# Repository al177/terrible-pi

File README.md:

# terrible-pi

*A supercomputer, but fun sized. And not super.*

In this repo you'll find hardware designs for the Terrible-Pi, a cluster
computer made from four Raspberry Pi Zero boards used as compute elements
and one Raspberry Pi Zero W as a head node and network router.

terrible-pi is based around a USB backplane that powers and interconnects
all five Pi Zeros and allows the head node to control power to each of the
compute nodes.  The USB boot feature of the Pi Zero is used to automate
deployment of new OS images to each compute node.

Up to date news on this project can be found at [this Hackaday project.](https://hackaday.io/project/27142-terrible-cluster)

Repo Contents
-------------
The terrible_pcb directory has a board design for the backplane and a 3D printable case.  See terrible_pcb/README for instructions for printing the case and the backplane board.

`etc` contains config files to be copied on top of the Raspbian install for
the head node.

wpa_supplicant.conf is a template WiFi config for the head node.  This is used
for headless setup of the head node Raspbian SD card for remote SSH access.

`nodeimg_build.sh` is a script for extracting a Raspbian distribution image into
a set of files used to deploy new compute nodes.

`node_init.sh` is a script used to upload the compute node Raspbian generated
by `nodeimg_build.sh` to the SD card of a compute node.

terrible-pi Install and Usage Guide
===================================

Setting up a terrible-pi cluster head node
------------------------------------------

1. Get the latest Raspbian (https://downloads.raspberrypi.org/raspbian_lite_latest)
   and install to a microSD
   
2. Mount the first (FAT) partition of the card on a PC.
		
3. Copy "wpa_supplicant.conf" from this repo to the card.  Edit it so that
   "YOUR_SSID" is replaced by the WiFi network name that you want the head node
   to connect to, and "YOUR_PASSPHRASE" is replaced by the network's key.  Use
   your Google-fu if you can't get it to work.
		
4. Create an empty file on the card named "ssh".  Use the UNIX command "touch
   ssh" or just open and save a new file "ssh" with your text editor.
		
5. Boot the microSD on the Pi Zero W
		
6. After 4-5 minutes, try SSHing as "pi" to the Zero W with the hostname
   "raspberrypi", "raspberrypi.lan", or "raspberrypi.local".  Use the password
   "raspberry".  If your router isn't serving DNS for local domains, you may
   have to check the router's DHCP lease logs to see what IP the head node has.
		
7. Now that you're logged into the Pi Zero W, update to the latest Raspbian
   packages:

```
sudo apt-get -y update && sudo apt-get -y upgrade
```
			
8. Install the necessary packages:
			
```
sudo apt-get -y install libusb-1.0-0-dev nfs-kernel-server git \
pdsh udhcpd iptables bridge-utils
```
9. Build and install the USB hub tool:

```
cd
git clone https://github.com/mvp/uhubctl.git
pushd uhubctl
make
sudo cp uhubctl /usr/local/bin/.
sudo chown root:root /usr/local/bin/uhubctl
popd
```
10. Build and install the USB boot tool:
	
```
git clone https://github.com/raspberrypi/usbboot.git
pushd usbboot
make
sudo cp rpiboot /usr/local/bin/.
sudo mkdir /usr/share/rpiboot
sudo cp -a msd /usr/share/rpiboot
sudo chown -R root:root /usr/share/rpiboot
sudo chown -R root:root /usr/local/bin/rpiboot
popd
```
11. Get this repo on the Pi:

```
git clone https://github.com/al177/terrible-pi.git
```

12. Copy the config files for the DHCP server, networks, NFS, SSH, and
hosts, hostname, and startup scripts:

```
sudo chown -R root:root /home/pi/terrible-pi/etc			
sudo cp -a /home/pi/terrible-pi/etc/* /etc/.
```		
13. Enable necessary services:

```
sudo systemctl enable udhcpd
sudo systemctl enable rpcbind
sudo systemctl enable nfs-kernel-server
```
14. Create an NFS directory for the clients:

```
sudo mkdir /srv/pihome
sudo chown pi:pi /srv/pihome
chmod 755 /srv/pihome
mkdir /srv/pihome/.ssh
chmod 700 /srv/pihome/.ssh
```

15. Reboot the head node.

16. SSH to the head node again. The config files copied over have changed the
    hostname to "head".  So if you connected as "raspberrypi.lan",
    "raspberrypi", or "raspberrypi.local" above, use "head.lan", "head", or
    "head.local" when reconnecting.

17. Make an empty passphrase SSH key so the head can automatically connect to
    the nodes:

```
ssh-keygen -t rsa -f /srv/pihome/.ssh/terrible.rsa -N ""
cp /srv/pihome/.ssh/terrible.rsa.pub /srv/pihome/.ssh/authorized_keys
chmod 600 /srv/pihome/.ssh/authorized_keys
mkdir -p ~/.ssh
chmod 700 ~/.ssh
cp /srv/pihome/.ssh/terrible.rsa ~/.ssh/.
```

Setting up terrible cluster compute nodes
-----------------------------------------

### Creating the compute node filesystem

1. Get the Raspbian Lite zip file on the head node in /home/pi.  This can be
   the zip used to create the head node microSD card, or can be downloaded by:

```
wget --trust-server-names https://downloads.raspberrypi.org/raspbian_lite_latest
```
	 
Note the filename that it downloads as.

2. Prep the boot image:

```
sudo terrible-pi/nodeimg_build.sh 2017-09-07-raspbian-stretch-lite.zip
```
	
This will take 10-15 minutes.  The result will be a directory "tcboot"
that contains the boot files and filesystems for the nodes.  This process
needs to be repeated only when changing or upgrading the Raspbian install on
the compute nodes.

### Deploying Raspbian to the compute nodes

1. Insure that the microSD cards in nodes do not contain the Raspberry Pi
   bootloader, or the USB boot method used to manage this cluster will not work.
   Insure that "bootcode.bin" does not exist in the root of any of the
   partitions on any of the cards.  If in doubt, do a full erase on the SD card
   to wipe out the bootloader in any of the partitions.
	 
2. Turn off all the nodes.  If the nodes all power up in bootstrap mode
   simultaneously, the image transfer script won't work.

```
sudo uhubctl -r 4 -a off
```

3. Transfer the SD filesystem to each node, looping over all nodes in series:

```
for N in 1 2 3 4; do sudo terrible-pi/node_init.sh tcboot $N; done
```

This takes 5-10 minutes per node depending on the speed of the SD cards
on the compute node Pi Zeros.

Terrible cluster management
---------------------------

### Booting the cluster

To boot the compute nodes, first start the rpiboot server in another
terminal session:

```
sudo rpiboot -o -l -d /home/pi/tcboot
```

Then cycle power on all of the nodes:

```
sudo uhubctl -r 4 -a cycle
```

The boot will take 2-3 minutes.  The nodes should be pingable once they are
done.  

### Connecting to the nodes

Before SSHing to a node in any given session, start the key agent and add
the SSH key:

```
eval `ssh-agent`
ssh-add ~/.ssh/terrible.rsa
```

You can SSH to a node by name:

```
ssh node1
```

Or you can run a command on all nodes with pdsh:

```
pdsh -R ssh -w node1,node2,node3,node4 hostname
```

Raspberry Pi Zero 1.3 models
[pi0computer.stl and pi0sdcard.stl](https://www.thingiverse.com/thing:2101674)
are created by jdhorvat and licensed CC-BY-NC.  [OpenSCAD parametric fan model](https://www.thingiverse.com/thing:625905) is created by GelatinousSlime and licensed CC-BY-SA. All other files in this tree are by Andrew Litt and licensed as 
[CC-BY-SA.](https://creativecommons.org/licenses/by-sa/4.0/)

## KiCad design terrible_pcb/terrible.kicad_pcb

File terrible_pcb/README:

Hardware design for the Terrible Cluster.

1) Backplane board

terrible.pro is the KiCad project for the Terrible Cluster backplane board.  All components needed to create fabbable output are in this project, however due to license restrictions the 3D models needed to render the assembly are not included.

Pre-built gerbers for the v0.1 release of the board are in the directory gerber_v0.1.  These are fab-ready and can be zipped and sent off as-is.

terrible_v1a_bom.csv is a CSV format BOM for the backplane.  It can be imported to a Digi-Key cart for convenience.

BOM history
-----------
v1  - Initial BOM for PCB v0.1
v1a - Corrected microUSB B to match the current footprint, add insulator
      spacer for crystal Y1

After assembling the backplane, flush cut all of the through hole pins to under 1mm, or it may not fit in the case.

2) Case

terrible_case.scad is an OpenSCAD model for a 3D printed enclosure for the Terrible Cluster.  It is a single piece into which the backplane and Zero nodes can slide.  A 40mm x 40mm x 10mm 5V fan is friction-fit into the open end, and provides cooling for the cluster.  The cluster board assembly is held in place by a piece of 1.75mm filament fed through holes at the open side of the backplane PCB channel.

terrible_case.stl is a printable file for the case rendered from terrible_case.scad.  This case is sensitive to printer tolerances, so if parts of the case print too tight or loose, it may be necessary to customize the SCAD file and regenerate the .stl.

The fan is wired to the two pin power pads on the backplane.  A 2x1 0.1" right angle header can be soldered to the pads, and a matching plug attached to the fan leads if desired, or the fan can be soldered directly to the pads.  Care should be taken to reduce slack in the fan cable to prevent any loose wire from interfering with the fan.

When sliding the cluster into the case, it may be necessary to move the Zeros side to side to get them to all fit in the slot cutouts.  It should not take much force to get the backplane to slide in all the way.

After the cluster is in the case, feed a piece of 1.75mm filament through both holes towards the back of the case.  Use flush cutters to clip the filament even with the side of the case on both sides.  This will prevent the cluster from sliding backwards into the fan, especially when inserting a microUSB power cable.  To take apart the cluster, push the filament through with a paperclip and pull it out from the other side.

The fan uses a friction fit to hold it in the back of the case.  Exact outer dimensions of these fans can vary slightly, so the fan cutout is intentionally slightly oversized.  Use a piece of folded paper or layers of tape on one side of the fan as a shim to secure the fan.

The SCAD file can render the case alone in an orientation for printing, or render the case along with a model of the cluster and the fan to show the finished cluster.  Set "PRODUCTION=true" near the top of the SCAD to render for printing, and "PRODUCTION=false" to render the internal parts as well.

3) Cluster model

terrible.scad is an OpenSCAD model of the backplane board and the Raspberry Pi Zeros.  It is used as part of the case model for checking fitment and to render a completed Terrible Cluster.  Load it into OpenSCAD on its own to render the cluster boards.

Attributions:

-Raspberry Pi Zero model by MisterC from https://www.thingiverse.com/thing:1638529 for the 3D model.

-OpenSCAD parametric fan model by GelatinousSlime from https://www.thingiverse.com/thing:625905 for the case model.

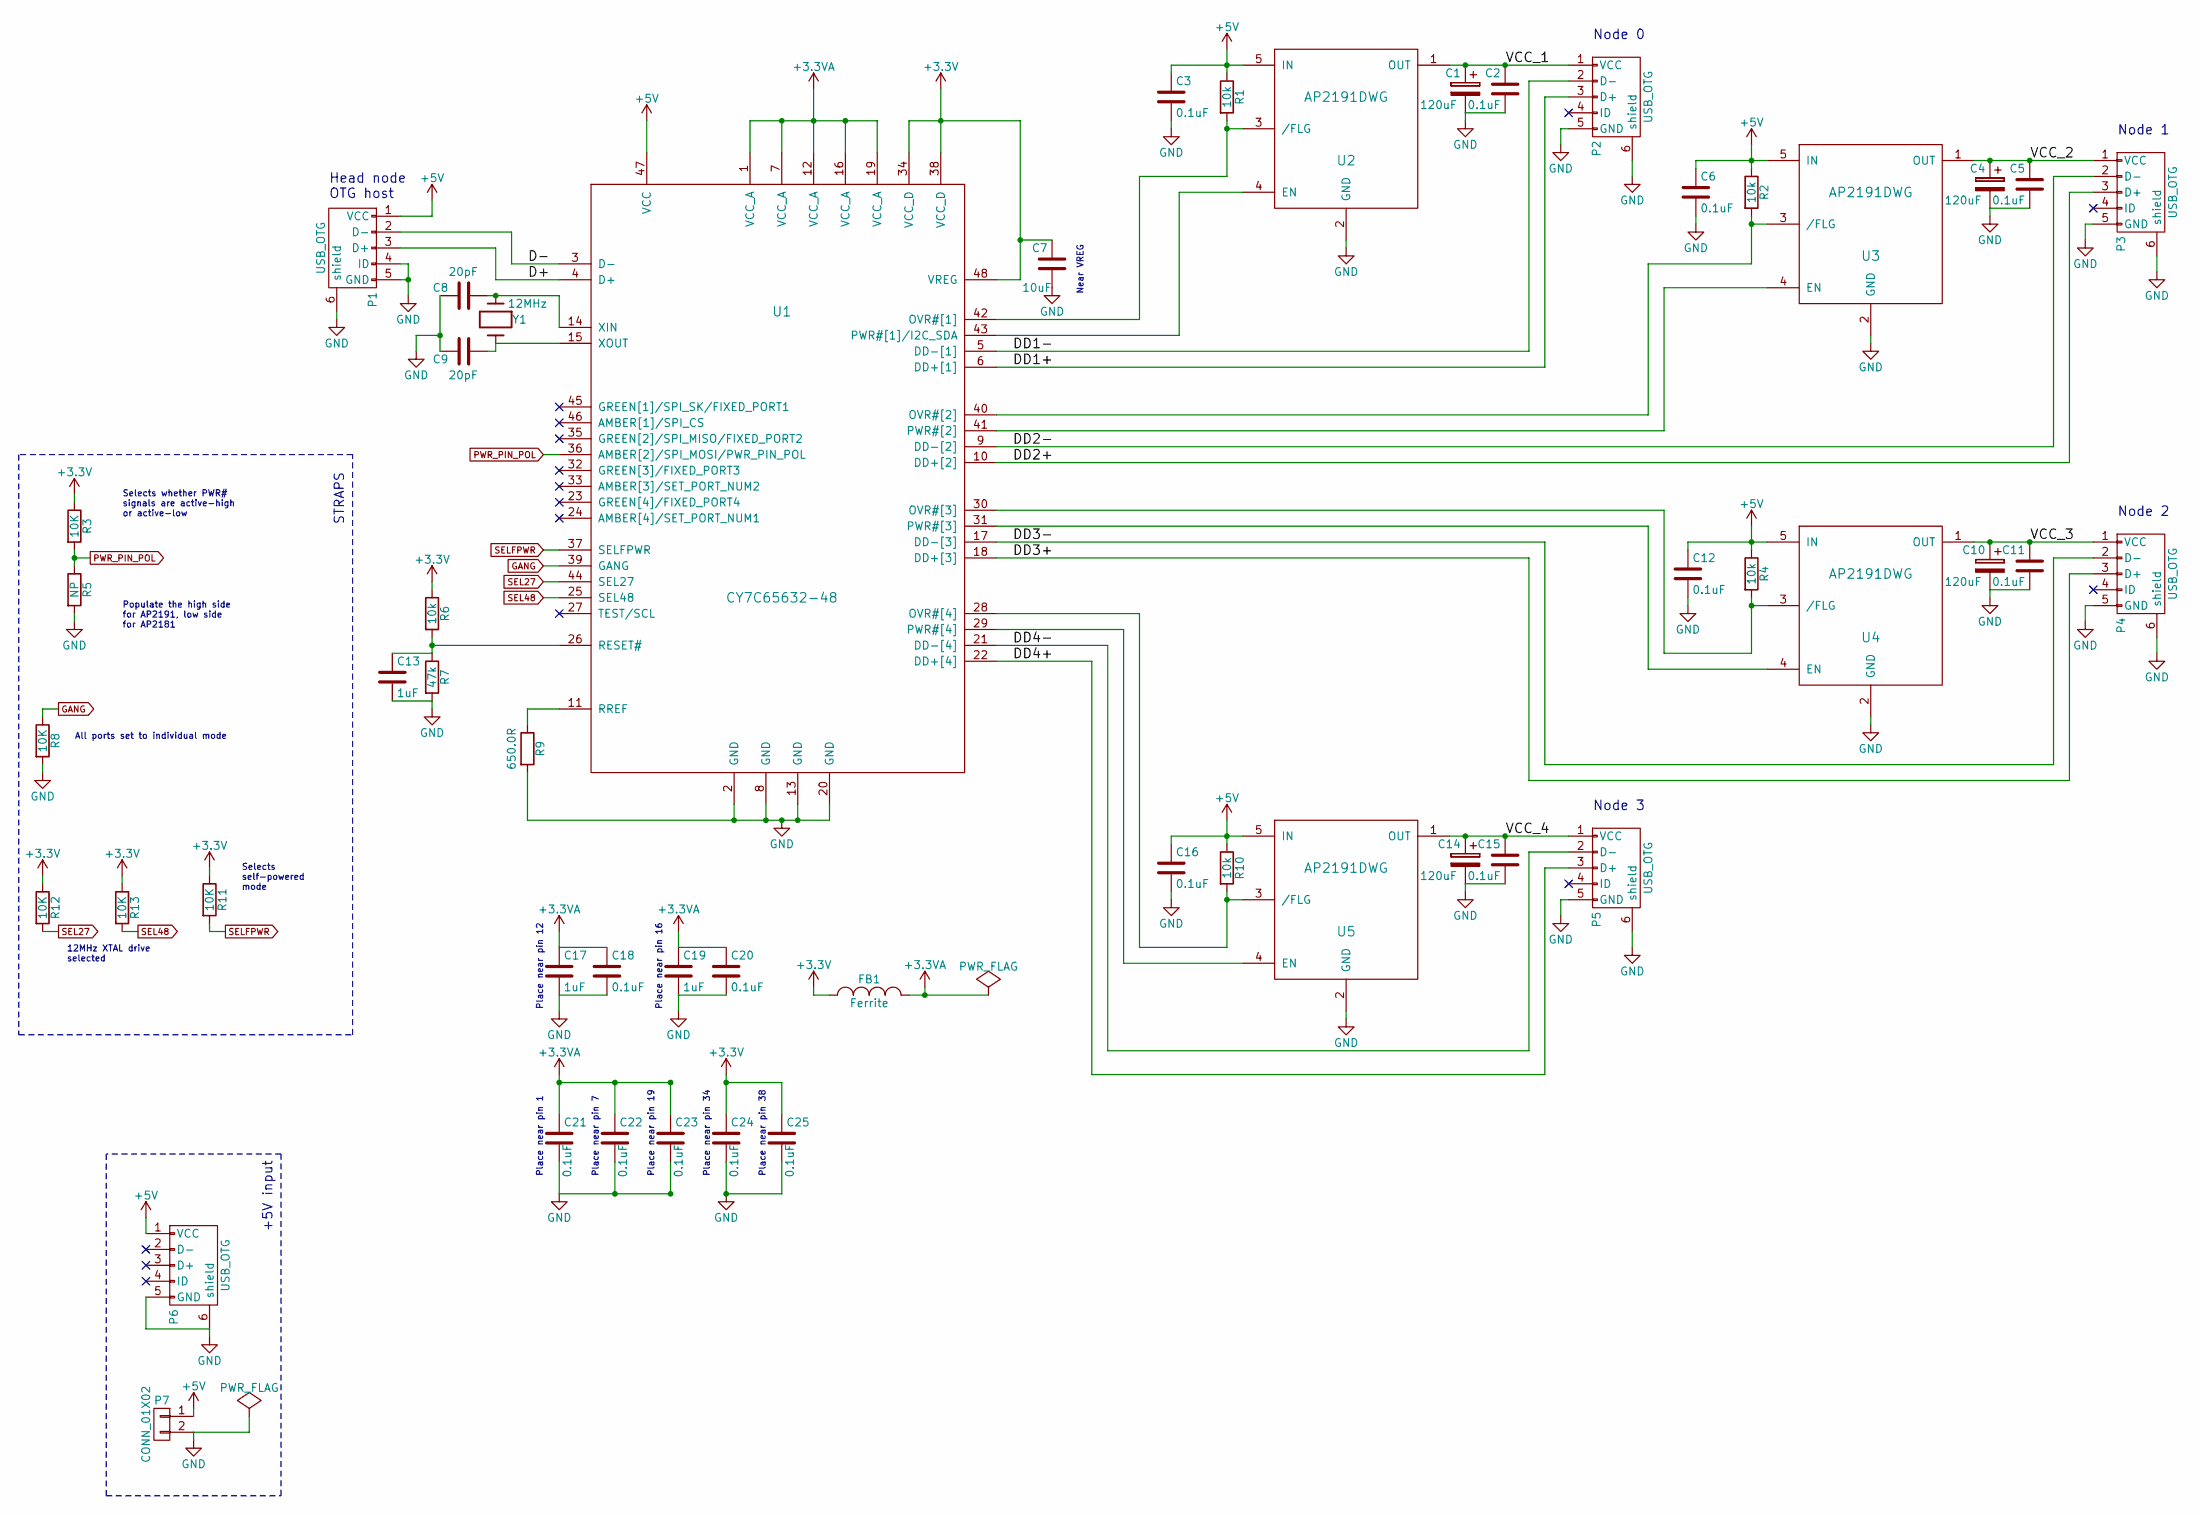
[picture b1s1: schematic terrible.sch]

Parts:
C1, C4, C10, C14: 120uF; C_Radial_D5_L11_P2.5
C2, C3, C5, C6, C11, C12, C15, C16, C18, C20, C21, C22, C23, C24, C25: 0.1uF; C_0805_HandSoldering
C7: 10uF; C_Radial_D5_L11_P2.5
C8, C9: 20pF; C_0805_HandSoldering
C13, C17, C19: 1uF; C_0805_HandSoldering
FB1: Ferrite; Choke_SMD_1206_Handsoldering
P1, P2, P3, P4, P5: USB_OTG; USB_Micro-B
P6: USB_OTG; USB_Micro-B_10103594-0001LF
P7: CONN_01X02; Pin_Header_Angled_1x02
R1, R2, R4, R6, R10: 10k; R_0603_HandSoldering
R3, R8, R11, R12, R13: 10K; R_0603_HandSoldering
R5: NP; R_0603_HandSoldering
R7: 47k; R_0603_HandSoldering
R9: 650.0R; R_0603_HandSoldering
U1: CY7C65632-48; TQFP-48_7x7mm_Pitch0.5mm
U2, U3, U4, U5: AP2191DWG; SOT-23-5
Y1: 12MHz; Crystal_HC49-SD_SMD

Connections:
+3.3VA: C17.1, C18.1, C19.1, C20.1, C21.1, C22.1, C23.1, FB1.1, U1.1 (VCC_A), U1.7 (VCC_A), U1.12 (VCC_A), U1.16 (VCC_A), U1.19 (VCC_A)
+3V3: C7.1, C24.1, C25.1, FB1.2, R3.1, R6.1, R11.1, R12.1, R13.1, U1.34 (VCC_D), U1.38 (VCC_D), U1.48 (VREG)
+5V: C3.1, C6.1, C12.1, C16.1, P1.1 (VCC), P6.1 (VCC), P7.1, R1.1, R2.1, R4.1, R10.1, U1.47 (VCC), U2.5 (IN), U3.5 (IN), U4.5 (IN), U5.5 (IN)
/D+: P1.3 (D+), U1.4 (D+)
/D-: P1.2 (D-), U1.3 (D-)
/DD1+: P2.3 (D+), U1.6 (DD+[1])
/DD1-: P2.2 (D-), U1.5 (DD-[1])
/DD2+: P3.3 (D+), U1.10 (DD+[2])
/DD2-: P3.2 (D-), U1.9 (DD-[2])
/DD3+: P4.3 (D+), U1.18 (DD+[3])
/DD3-: P4.2 (D-), U1.17 (DD-[3])
/DD4+: P5.3 (D+), U1.22 (DD+[4])
/DD4-: P5.2 (D-), U1.21 (DD-[4])
/VCC_1: C1.1, C2.1, P2.1 (VCC), U2.1 (OUT)
/VCC_2: C4.1, C5.1, P3.1 (VCC), U3.1 (OUT)
/VCC_3: C10.1, C11.1, P4.1 (VCC), U4.1 (OUT)
/VCC_4: C14.1, C15.1, P5.1 (VCC), U5.1 (OUT)
GANG: R8.1, U1.39 (GANG)
GND: C1.2, C2.2, C3.2, C4.2, C5.2, C6.2, C7.2, C8.2, C9.2, C10.2, C11.2, C12.2, C13.2, C14.2, C15.2, C16.2, C17.2, C18.2, C19.2, C20.2, C21.2, C22.2, C23.2, C24.2, C25.2, P1.4 (ID), P1.5 (GND), P1.6 (shield), P2.5 (GND), P2.6 (shield), P3.5 (GND), P3.6 (shield), P4.5 (GND), P4.6 (shield), P5.5 (GND), P5.6 (shield), P6.5 (GND), P6.6 (shield), P7.2, R5.2, R7.2, R8.2, R9.2, U1.2 (GND), U1.8 (GND), U1.13 (GND), U1.20 (GND), U2.2 (GND), U3.2 (GND), U4.2 (GND), U5.2 (GND)
unnamed: C8.1, U1.14 (XIN), Y1.1
unnamed: C9.1, U1.15 (XOUT), Y1.2
unnamed: C13.1, R6.2, R7.1, U1.26 (RESET#)
unnamed: R1.2, U1.42 (OVR#[1]), U2.3 (/FLG)
unnamed: R2.2, U1.40 (OVR#[2]), U3.3 (/FLG)
unnamed: R4.2, U1.30 (OVR#[3]), U4.3 (/FLG)
unnamed: R9.1, U1.11 (RREF)
unnamed: R10.2, U1.28 (OVR#[4]), U5.3 (/FLG)
unnamed: U1.29 (PWR#[4]), U5.4 (EN)
unnamed: U1.31 (PWR#[3]), U4.4 (EN)
unnamed: U1.41 (PWR#[2]), U3.4 (EN)
unnamed: U1.43 (PWR#[1]/I2C_SDA), U2.4 (EN)
PWR_PIN_POL: R3.2, R5.1, U1.36 (AMBER[2]/SPI_MOSI/PWR_PIN_POL)
SEL27: R12.2, U1.44 (SEL27)
SEL48: R13.2, U1.25 (SEL48)
SELFPWR: R11.2, U1.37 (SELFPWR)

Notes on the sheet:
Head node OTG host
Node 0
Node 1
Node 2
Node 3
Populate the high side for AP2191, low side for AP2181
Selects whether PWR# signals are active-high or active-low
All ports set to individual mode
12MHz XTAL drive selected
Selects self-powered mode
STRAPS
Place near pin 12
Place near pin 16
Place near pin 1
Place near pin 7
Place near pin 19
Place near pin 34
Place near pin 38
Near VREG
+5V input

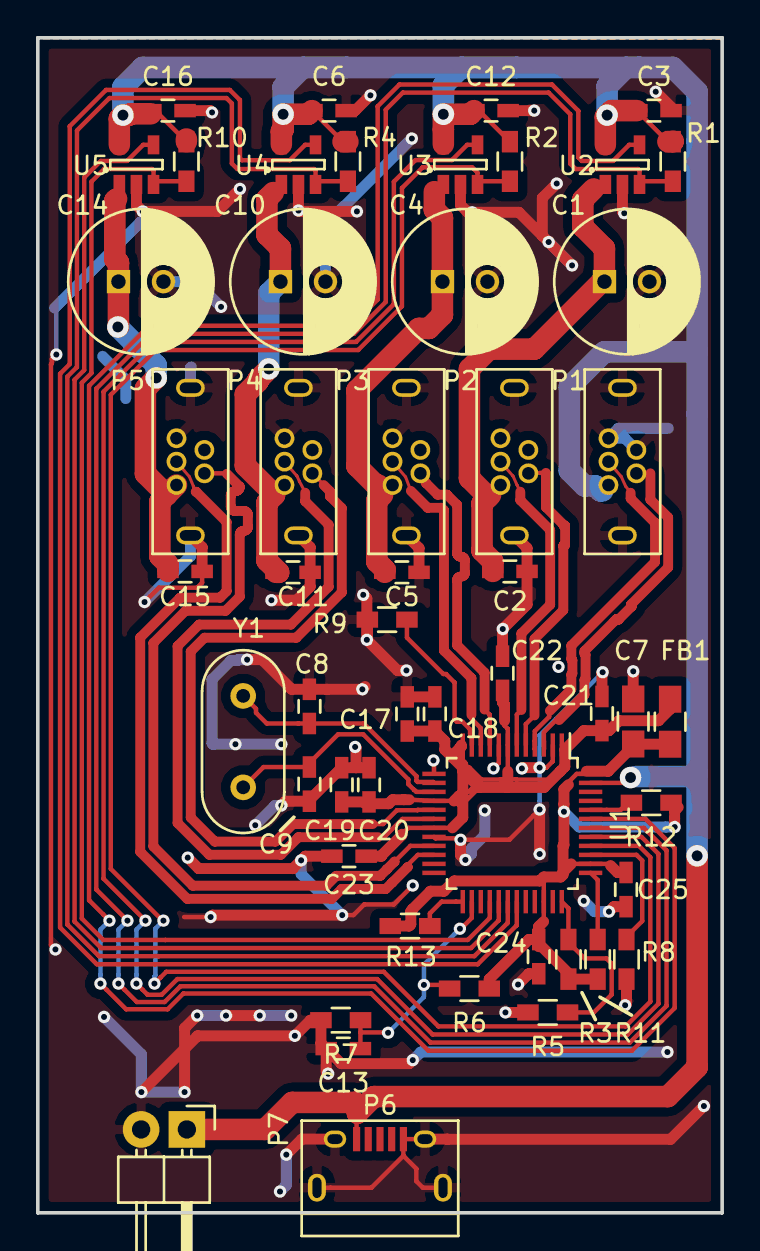
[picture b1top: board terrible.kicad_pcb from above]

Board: 2 copper layers, 38.0 x 65.3 mm, 52 parts (0 on the bottom side), 35 nets.

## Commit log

2017-09-05 Initial commit. Includes first pass PCB gerbers
2017-09-05 Add README with Pi Zero model attribution, render, and schematic PDF.
2017-09-05 Minor README edit
2017-09-30 Add in untested procedure and files for creating the cluster
2017-09-30 Add dummy wpa_supplicant.conf for easy headless Pi Zero W configuration
2017-09-30 Add network interface configuration
2017-09-30 Move misplaced dhcp server config file
2017-09-30 Remove network interface definitions from /etc/network/interfaces since we're using interfaces.d
2017-09-30 Fix network wlan config and deny the DHCP client from getting an address from our own server
2017-09-30 Documentation fixes
2017-09-30 Remove unneeded nfs export
2017-09-30 Don't need the wifi in the global interfaces file after all
2017-09-30 More install procedure updates
2017-10-01 Clean up notes file formatting
2017-10-02 Remove old model
2017-10-02 Start on printed case
2017-10-16 Case in progress checkpoint
2017-10-17 Add fan to enclosure, still not complete
2017-10-17 Add parametric DC box fan model
2017-10-19 Integrated fan case
2017-10-19 Case and PCB documentation updates
2017-10-19 Add the DigiKey BOM
2017-10-19 Update build directions to use mainline usbboot
    The devicetree overlay directory support for usbboot has been merged to the mainline from burtyb's repo, so use mainline instead.
2017-10-20 Switch to the lightweight udhcpd package for the DHCP server
2017-11-12 microUSB-B connector in BOM now fits the PCB
2017-11-12 Update BOM version, add spacer for crystal
2017-12-16 Update README.md
    Add some pictures
2018-01-24 Increase USB MTU for jumbo frames, automatically find keyfile when sshing between nodes
2018-01-25 Linux RNDIS gadget and device driver goes to 15000, so crank it up
2018-02-05 New head setup via Ansible
2018-02-08 Add playbook for partial node image creation
2020-10-15 Add bits from an old HPL demo that runs on this cluster
2020-10-17 Updates for Raspbian Buster - not quite reliable at the moment
2020-10-18 Fixes to HPL procedures & switch to openmpi from MPICH due to segfaults from MPICH
2020-10-19 Disable throttling before starting HPL for an extra 8% performance in the bench
2021-03-02 Overhaul Ansible head node install flow
2025-06-03 Automate head node setup based on procedure in README - update for RaspiOS
2025-06-03 Update for RaspiOS - not working yet
